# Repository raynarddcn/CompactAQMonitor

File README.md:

# CompactAQMonitor
A portable device designed to monitor Air Quality parameters inside a room with high accuracy and zero drift. Built around a custom PCB, powered by ESP32-S2. Sensors consists of SHT40, SGP40, SPS30, and SenseAir S88, and combined wiht ILI9341 Touchscreen LCD inside 3D printed enclosure

# Features
- True CO2 Sensing with NDIR: This devices uses a Senseair S88 Residential sensor for accurately measuring CO2 using Non-Dispersive Infrared, rather than deriving the data like CO2 Equivalent sensors
- Precise VOC, Temperature, and RH Tracking: this device uses the Sensirion SGP40 TVOC&NoX sensor (DFRobot Module) to accurately measure VOC levels inside a room, paired with the SHT40 to measure Temp & RH.
- PM Monitoring: This device uses a Sensirion SPS30 to track the Particulate Matter, because the SPS30 is contamination resistant with filter before air goes into the laser sensor
- Interactive 2.8inch TFT Display: Uses the ILI9341 with XPT2046 Touch display for interactive viewing
- Modular Hardware: Nothing is soldered on, just using female headers to solder the components, there is also expandable IO to add more sensors (using unpopulated GPIO pins)
# Background
I am living in a high-density dorm room with closed windows, which causes indoor air quality to plummet rapidly (especially CO2). High CO2 levels can lead to sleep disruption which causes fatigue and brain fog. Cheap sensors usually fake the CO2 data using derived values to estimate CO2 which is prone to fail and be innacurate.
CompactAQMonitor is designed as an accurate and reliable sensor & desk companion without spending too much money as a real air quality monitor, but still get the core features.

# Images

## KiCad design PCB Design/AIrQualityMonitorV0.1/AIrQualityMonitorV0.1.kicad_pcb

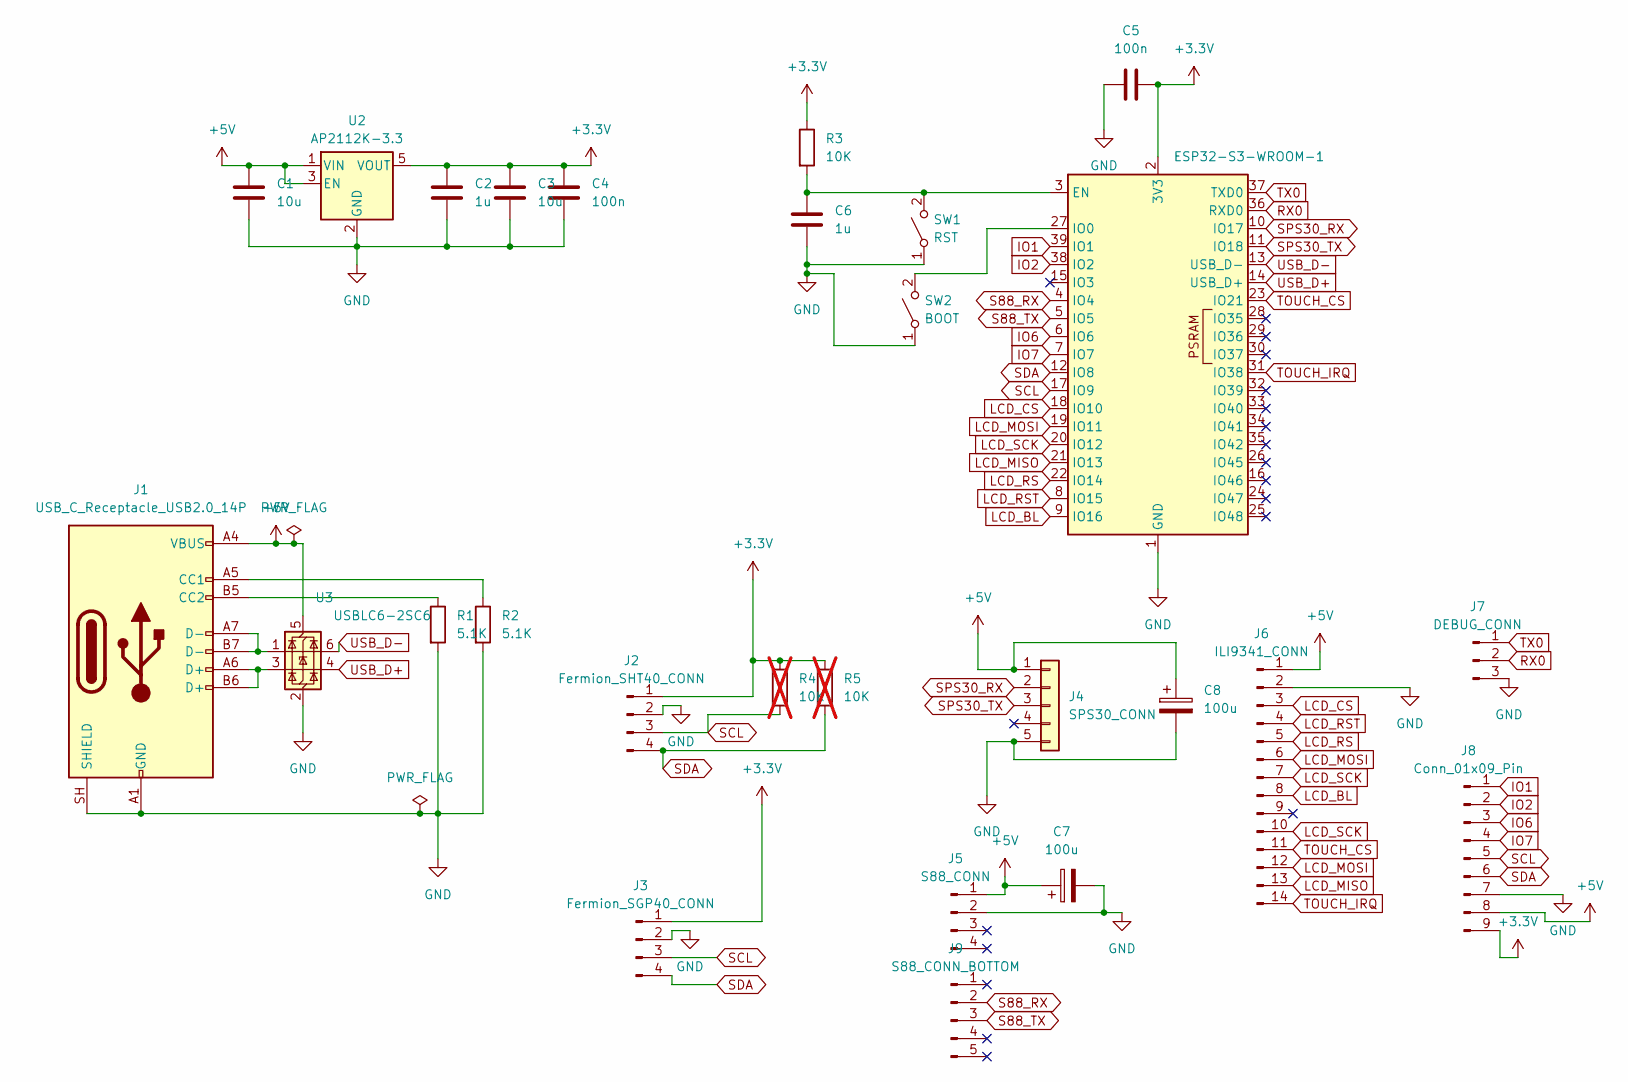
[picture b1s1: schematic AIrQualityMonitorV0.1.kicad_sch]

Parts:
C1, C3: 10u; C_0805_2012Metric
C2, C6: 1u; C_0603_1608Metric
C4, C5: 100n; C_0603_1608Metric
C7, C8: 100u; C_Elec_6.3x5.4
J1: USB_C_Receptacle_USB2.0_14P; USB_C_Receptacle_HRO_TYPE-C-31-M-12
J2: Fermion_SHT40_CONN; PinSocket_1x04_P2.54mm_Horizontal
J3: Fermion_SGP40_CONN; PinSocket_1x04_P2.54mm_Vertical
J4: SPS30_CONN; JST_ZH_B5B-ZR_1x05_P1.50mm_Vertical
J5: S88_CONN; PinSocket_1x04_P2.54mm_Vertical
J6: ILI9341_CONN; PinSocket_1x14_P2.54mm_Vertical
J7: DEBUG_CONN; PinHeader_1x03_P2.54mm_Vertical
J8: Conn_01x09_Pin; PinHeader_1x09_P2.54mm_Vertical
J9: S88_CONN_BOTTOM; PinSocket_1x05_P2.54mm_Vertical
R1, R2: 5.1K; R_0603_1608Metric
R3: 10K; R_0603_1608Metric
R4, R5: 10K; R_0603_1608Metric; not fitted
SW1: RST; SW_SPST_PTS645Sx43SMTR92
SW2: BOOT; SW_SPST_PTS645Sx43SMTR92
U1: ESP32-S3-WROOM-1
U2: AP2112K-3.3; SOT-23-5
U3: USBLC6-2SC6; SOT-23-6

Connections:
+3.3V: C2.1, C3.1, C4.1, C5.1, J2.1, J3.1, J8.9, R3.1, R4.2, R5.1, U1.2 (3V3), U2.5 (VOUT)
+5V: C1.1, C7.1, C8.1, J1.A4 (VBUS), J1.A9 (VBUS), J1.B4 (VBUS), J1.B9 (VBUS), J4.1, J5.1, J6.1, J8.8, U2.1 (VIN), U2.3 (EN), U3.5 (VBUS)
GND: C1.2, C2.2, C3.2, C4.2, C5.2, C6.2, C7.2, C8.2, J1.A1 (GND), J1.A12 (GND), J1.B1 (GND), J1.B12 (GND), J1.SH (SHIELD), J2.2, J3.2, J4.5, J5.2, J6.2, J7.3, J8.7, R1.2, R2.2, SW1.1 (A), SW2.1 (A), U1.1 (GND), U1.40 (GND), U1.41 (GND), U2.2 (GND), U3.2 (GND)
IO1: J8.1, U1.39 (IO1)
IO2: J8.2, U1.38 (IO2)
IO6: J8.3, U1.6 (IO6)
IO7: J8.4, U1.7 (IO7)
LCD_BL: J6.8, U1.9 (IO16)
LCD_CS: J6.3, U1.18 (IO10)
LCD_MISO: J6.13, U1.21 (IO13)
LCD_MOSI: J6.6, J6.12, U1.19 (IO11)
LCD_RS: J6.5, U1.22 (IO14)
LCD_RST: J6.4, U1.8 (IO15)
LCD_SCK: J6.7, J6.10, U1.20 (IO12)
unnamed: J1.A5 (CC1), R2.1
unnamed: J1.B5 (CC2), R1.1
unnamed: J1.A6 (D+), J1.B6 (D+), U3.3 (I/O2)
unnamed: J1.A7 (D-), J1.B7 (D-), U3.1 (I/O1)
unnamed: C6.1, R3.2, SW1.2 (B), U1.3 (EN)
unnamed: SW2.2 (B), U1.27 (IO0)
RX0: J7.2, U1.36 (RXD0)
S88_RX: J9.2, U1.4 (IO4)
S88_TX: J9.3, U1.5 (IO5)
SCL: J2.3, J3.3, J8.5, R4.1, U1.17 (IO9)
SDA: J2.4, J3.4, J8.6, R5.2, U1.12 (IO8)
SPS30_RX: J4.2, U1.10 (IO17)
SPS30_TX: J4.3, U1.11 (IO18)
TOUCH_CS: J6.11, U1.23 (IO21)
TOUCH_IRQ: J6.14, U1.31 (IO38)
TX0: J7.1, U1.37 (TXD0)
USB_D+: U1.14 (USB_D+), U3.4 (I/O2)
USB_D-: U1.13 (USB_D-), U3.6 (I/O1)

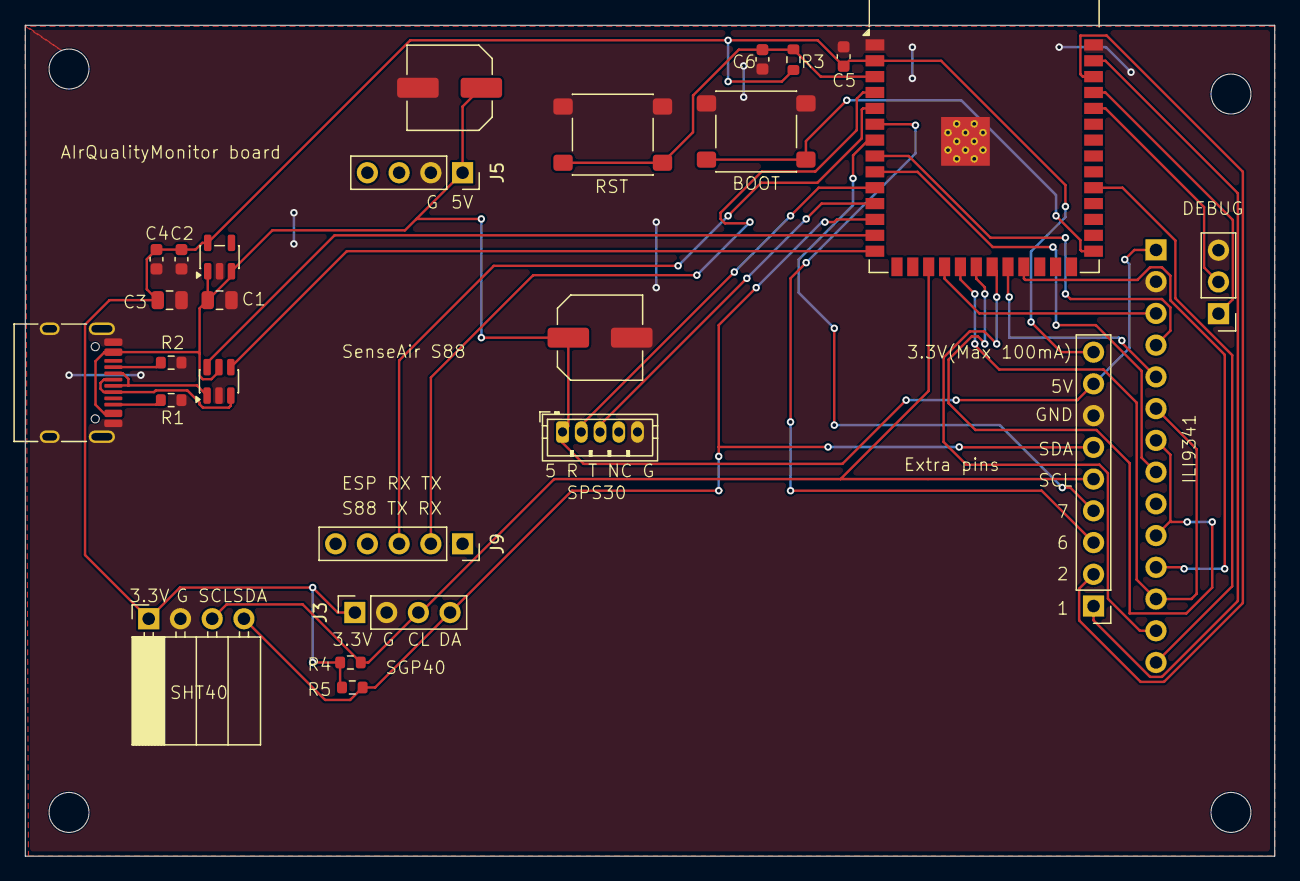
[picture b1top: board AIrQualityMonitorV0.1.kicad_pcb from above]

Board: 2 copper layers, 100.0 x 66.5 mm, 27 parts (1 on the bottom side), 32 nets.
